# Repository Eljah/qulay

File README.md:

# Qulay / Кулай

**QL-01.R1 + C1 — открытый инженерный прототип контактного профилометра доступной среды.** Тележка с 31 независимым роликом измеряет переход «дорога — бордюрный съезд — тротуар». Результат — исходные отсчёты, геометрия, пропуски и воспроизводимый отчёт, а не неподтверждённое заключение о приёмке.

Рабочая ветка: `feature/qulay-prototype-20261002`. Исходная история сохранена; `main` не заменяется. **Это ещё не производственный комплект всей тележки и не метрологически утверждённый прибор.**

## Актуальное соединение рычага с валом: C1

Предупреждение в документах R1 о неразработанном соединении рычага с валом относится к исторической конструкции. Теперь для этого узла разработан **C1: цельный фланцевый вал, два установочных штифта Ø3 и два прижимных винта M3**. Передача момента не опирается на трение стянутых торцов. Детали, посадки, сборка и критерии стендового контроля описаны в отдельном комплекте; физические испытания ещё не выполнены.

**[PDF C1: пояснение и размерные чертежи](mechanical/coupling_c1/generated/Qulay_C1_Lever_Shaft_Coupling.pdf)** · **[Весь комплект STEP/DXF и отчётов](mechanical/coupling_c1/generated)** · **[Описание конструкции и изготовления](mechanical/coupling_c1/README.md)** · **[Область изменения C1](docs/REVISION_C1.md)**

В каталоге C1 находятся обычные файлы, а не архив вместо проекта: отдельные STEP деталей и соединения, три STEP-сборки тележки с установленным C1, DXF рычага и карты отверстий фланца, PDF, BOM, расчёт, проверка пересечений и контрольные суммы. Старые модели R1 сохранены для сравнения; они не заменяют сборки с C1.

## Что открывать

| Часть | Содержимое |
|---|---|
| [C1: соединение рычага с валом](mechanical/coupling_c1) | Цельный фланцевый вал, штифты и винты; исходники, детали, посадки и порядок сборки |
| [C1: готовые файлы](mechanical/coupling_c1/generated) | PDF с тремя листами A3, STEP деталей и трёх положений тележки, DXF, BOM и проверки |
| [Руководство по механике и монтажу R1](docs/manual) | Историческая базовая инструкция; для соединения рычаг–вал применять дополнение C1 |
| [Один ролик, tilt и AS5048A](docs/channel) | Принцип измерения, магнит, SPI и преобразование угла; статус соединения уточнён ссылкой на C1 |
| [CAD ревизии R1](mechanical/generated-r1) | Три исторические STEP-сборки, реальные CAD-виды и разрез, DXF кронштейна, реестры, отчёты пересечений |
| [PDF узла и сборок R1](mechanical/generated-r1/QL01-R1-review.pdf) | Крупные изображения исходной ревизии; соединение рычаг–вал заменено в C1 |
| [Первоначальный комплект](mechanical/generated) | Исходные модели, альбом A3, DXF рычага и реестры; не удалены |
| [Плата датчика](electronics/generated/encoder) | KiCad-проект, схема PDF, PCB/SVG, Gerber/Excellon прототипа, ERC/DRC и netlist |
| [Плата сбора с Pico](electronics/generated/carrier) | KiCad-проект R1 для подключения четырёх цепочек датчиков, ADXL355-модуля, одометра и USB |
| [Прошивка](firmware) | RP2040/Pico SDK, сборка UF2/ELF в Actions; C, не Java |
| [Java/Maven](software) | core, сервер Spring Boot, desktop Swing, агент SBC и геометрический симулятор |
| [Подтверждение тестов R1](generated/verification/summary.json) | 52 модульных теста и 12 end-to-end проверок на момент R1; commit и run ID внутри отчёта |
| [Изменения и ограничения R1](docs/REVISION_R1.md) | История исправлений и исходные ограничения; дополнение по соединению — C1 |

Редактируемый CAD-источник C1: [mechanical/coupling_c1/build.py](mechanical/coupling_c1/build.py), использующий [mechanical/revision_b.py](mechanical/revision_b.py) и исходный [build.py](mechanical/build.py). Это CadQuery/OpenCascade + STEP, не вымышленный проект, якобы сохранённый из SolidWorks.

## Архитектура базового программно-измерительного контура R1

```mermaid
flowchart LR
  Rollers[31 ролик + AS5048A] -->|SPI: 8+8+8+7| Pico[Pico / RP2040 · C]
  Tilt[ADXL355-модуль] -->|SPI| Pico
  Odo[Одометр 3.3 V] --> Pico
  Pico -->|USB CDC + CRC32| SBC[Linux SBC · Java 21]
  SBC -->|Wi-Fi / HTTPS| Server[Spring Boot · планы и обследования]
  SBC -->|JSON + SHA-256 + сырой журнал| USB[Съёмный накопитель]
  USB --> Desktop[Swing · просмотр и загрузка]
  Desktop -->|HTTPS| Server
  Server -->|План обследования| Desktop
  Desktop -->|План + SHA-256| USB
```

Основной компьютер — Raspberry Pi/совместимый Linux SBC; измерительный опрос вынесен в Pico. Специальное мобильное приложение не требуется: телефон может предоставлять Wi-Fi-точку доступа. Полностью автономный мобильный интернет предполагает отдельный USB LTE-модем и настройку Linux; собственная ВЧ-плата и проверенный LTE-комплект в R1 не заявлены. Выпуск C1 изменяет механическое соединение, а не этот контур связи.

## Что измеряется

X — направление прохода, Y — положение канала поперёк тележки, Z — высота. Угол рычага — исходное измерение, **не ось Y и не готовый уклон поверхности**. При пересчёте изменяются и X, и Z точки контакта; наклоны рамы также учитываются.

`CROSSING`: движение поперёк бордюра. Для достоверного продольного профиля нужна независимая высотная база. `ALONG_CURB`: часть роликов на дороге, часть на тротуаре; анализируется разность площадок и смещение контактов по X. `FREE_ROLL` не становится строгим продольным нивелированием только благодаря IMU.

Габариты проекта: 31 канал × шаг 25 мм; 750 мм между крайними осями; наружная ширина по осям крепежа 870 мм; рычаг 240 мм; ролики с короной R20, ширина 12 мм. Это принятые проектные значения, не универсальные нормативы размеров инвалидного кресла.

Одного прохода шириной 750 мм недостаточно для доказательства доступности всей ширины съезда. Вертикальная грань, потеря контакта и ненаблюдаемая область сохраняются как отдельные состояния, а не превращаются сглаживанием в удобный пандус.

## Сборка и запуск

Нужны **JDK 21 и Maven**. Старые JDK 12/17 не соответствуют текущей сборке.

```bash
git clone --branch feature/qulay-prototype-20261002 https://github.com/Eljah/qulay.git
cd qulay
mvn -B verify
java -jar software/simulator/target/simulator-0.1.0.jar generated/demo
java -jar software/desktop/target/desktop-0.1.0.jar
```

В desktop откройте JSON из `generated/demo/surveys` рядом с его `.sha256`. Есть матрица всех 31 каналов, выбор продольного профиля, отдельный просмотр сырых углов, выгрузка CSV, загрузка на сервер и запись плана на флешку. Серые ячейки — недостоверные/пропущенные точки. Данные симулятора явно отмечены как синтетические.

Сервер Linux/macOS:

```bash
export QULAY_TOKEN="$(openssl rand -hex 32)"
java -jar software/server/target/server-0.1.0.jar
```

Windows PowerShell:

```powershell
$env:QULAY_TOKEN = [guid]::NewGuid().ToString('N') + [guid]::NewGuid().ToString('N')
java -jar software/server/target/server-0.1.0.jar
```

Веб-интерфейс: `http://127.0.0.1:8080/`. Введите свой токен. Для удалённого доступа нужен HTTPS reverse proxy и отдельная настройка безопасности. У сервера нет универсального встроенного пароля; по умолчанию он слушает только loopback. Перед публичным развёртыванием требуется проверка актуальности зависимостей и эксплуатационный аудит.

Загрузка накопленных проходов:

```bash
java -jar software/agent/target/agent-0.1.0.jar sync generated/demo/surveys http://127.0.0.1:8080
```

Команда использует `QULAY_TOKEN` из окружения. Повторная отправка тех же байтов идемпотентна. Другие данные с тем же UUID отвергаются.

## Захват с реальной платы

Сначала получите план из сервера через desktop или `agent pull-plan`. Для захвата нужен `plan.json` с парным `.sha256`, а также индивидуальная калибровка 31 канала, не синтетический шаблон.

```bash
java -jar software/agent/target/agent-0.1.0.jar capture /dev/ttyACM0 calibration.json plan.json 1000 /media/usb/QULAY/surveys 10 0
```

Последние параметры: тайм-аут полного кадра в секундах и индекс объекта плана с нуля. Незавершённый проход остаётся `.wire.partial`; законченный получает JSON/SHA-256 и сырой журнал. Устройства в Q1 ещё не имеют подтверждённого контроля контакта: CONTACT_UNKNOWN сохраняется и блокирует положительное заключение.

## Проверки, которые действительно выполняются

**Программа:** модульные тесты геометрии, CRC, обработки данных, тайм-аутов и неполных проходов. E2E поднимает реальный JVM-сервер, проверяет авторизацию, хеши, повторы, конфликт UUID, планы, синхронизацию и сохранность после перезапуска. Скриншоты — пиксели настоящего окна Swing в Xvfb с синтетическим входом.

**Электроника:** реально запущены трассировщик и KiCad. Проверяются ERC, DRC, отсутствие неразведённых соединений и соответствие каждого подключённого вывода исходной таблице, схеме и PCB. [Отчёт R1](electronics/generated/verification-summary.json). Это не аналоговая симуляция и не испытание собранной платы.

**Механика R1:** три соседних канала в трёх статических положениях проверяются на пересечения твёрдых тел. [Отчёт R1](mechanical/generated-r1/collision-checks.json) и [проблемы исходной сборки](mechanical/generated-r1/original-interference.json). Это не FEA и не проверка всех зазоров тележки во всём диапазоне движения.

**Соединение C1:** сохранены [проверка твёрдых тел и 19 угловых положений](mechanical/coupling_c1/generated/verification.json) и [расчёт с консервативным нагружением одного штифта](mechanical/coupling_c1/generated/calculations.json). Отчёты относятся к указанному узлу и сохранённым соседям R1. Статический расчёт и CAD-проверка не подтверждают ресурс и фактический люфт изготовленного экземпляра.

Бинарные JAR/UF2/ELF и полные журналы доступны в [GitHub Actions](https://github.com/Eljah/qulay/actions). Артефакты Actions имеют срок хранения; CAD, схемы, отчёты и исходники сохранены также обычными файлами Git. Скрипт публикации не делает force-push и отказывается публиковать устаревшую сборку при изменении её входных файлов.

## До полевой приёмки

Соединение рычага с валом конструктивно определено выпуском C1; остаются изготовление согласованной пары и физический контроль. Не закрыты физические испытания трёхканального узла, осевая фиксация всего вала в корпусе, окончательное крепление магнита, реальные пружины/замки/уплотнения и прочий крепёж, контроль контакта, калибровка магнитных датчиков, проверка высотной базы под нагрузкой и методика оценки неопределённости. Профиль `DEMO-ONLY-01` — демонстрационный, не набор подтверждённых нормативных пределов. `acceptanceEligible` остаётся false.

[Концепция](docs/CONCEPT.md) · [Метрология](docs/METROLOGY.md) · [Подробности R1](docs/REVISION_R1.md) · [Соединение C1](docs/REVISION_C1.md) · [Прошивка и распиновка](firmware/README.md)

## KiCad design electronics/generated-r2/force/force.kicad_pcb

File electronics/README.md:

# Электронная сборка QL-01

## Архитектура

Raspberry Pi 4 / Linux SBC выполняет Java-агент, хранение, связь и работу с флеш-памятью. Pico RP2040 подключён к нему по USB CDC и опрашивает измерительные датчики. Специальное мобильное приложение не требуется: телефон может предоставить Wi-Fi hotspot; опционально используется готовый сертифицированный USB LTE-модем. Разработка собственного GSM-тракта не входит в QL-01.

Редактируемые проекты KiCad создаются `build_checked.py`: плата углового датчика `encoder` 18×24 мм, плата сопряжения Pico `carrier` 80×100 мм. Схемы и платы создаются из одной таблицы выводов, поэтому в `connections.csv` есть явная проверяемая карта каждого контакта. `harness.csv` задаёт все 31 канала, цепочки 8+8+8+7. Изображение платы без электрических сетей не выдаётся за разработанную схему.

## Основные узлы и количества

| Узел | Количество | Примечание |
|---|---:|---|
| Raspberry Pi 4 / Linux SBC | 1 | Java 21, USB, Wi-Fi; отдельное питание |
| Raspberry Pi Pico RP2040 | 1 | Нативный USB; две SPI-шины |
| AS5048A, TSSOP14 | 31 | По одному на каждый шарнир |
| encoder PCB | 31 | AS5048A, 100 нФ, 10 мкФ, разъём |
| carrier PCB | 1 | Разъёмы Pico, датчиков, питания, одометра |
| Диаметрально намагниченный магнит | 31 | Геометрия и материал согласуются по испытанию |
| ADXL355, модуль с доступным SPI 3.3 В | 1 | Жгут согласно нашей распиновке; не обещается прямое совпадение с любым модулем |
| Квадратурный энкодер 3.3 В | 1 | Реальное колесо и масштаб калибруются; 12/24 В входы не поддержаны |
| Внешний стабилизатор датчиков 3.3 В | 1 | Ток не менее 1 А как проектный запас, с ограничением тока |
| Питание SBC 5 В | 1 | Проектный бюджет до 4 А с запасом и отдельной проверкой пиков USB |
| Готовая батарея с BMS/защитой | 1 | Не проект самостоятельной сборки литиевых ячеек |

31 AS5048A при типовом потреблении порядка 15 мА требуют около 465 мА, без запаса. Не подключать их все к 3V3 Pico. Carrier принимает отдельные 3.3 В через PTC; номинал PTC и температурное снижение допустимого тока должны быть проверены. Pico питается от USB, общая земля соединена. Отключённое питание датчиков при активных SPI-линиях может вызывать паразитное питание через входы: порядок включения, буфер/изоляция и защита линий подлежат проверке перед полевым прибором.

Оценочный рабочий бюджет всей электроники 12–20 Вт, не измеренный. Для батареи 60 Вт·ч и суммарного использования 80% это примерно 2.4–4 часа; холод и LTE могут ухудшить результат. Номинал батареи выбирается после замера фактического потребления и пиков.

## Монтаж и первичное включение

Сначала USB-Pico без датчиков: загрузить UF2, проверить CDC и период строк. Затем один AS5048A от ограниченного источника 3.3 В; проверить распиновку, паритет, OCF и диагностику магнита при полном диапазоне поворота. Затем три соседних канала и влияние магнитов. Только после этого — все цепочки и нагрузочное питание. Физическое движение одного рычага должно менять именно его индекс в журнале, иначе порядок SPI-цепочки не подтверждён.

AS5048A SPI mode 1, ADXL355 SPI mode 0: они намеренно на разных контроллерах. Жгуты сигнала и земли прокладывать совместно, питание вести с достаточным сечением; окончательные длины, фронты, резисторы согласования, ESD и EMC подтверждаются на приборе. Наружный USB и разъёмы должны иметь механическую разгрузку и защиту от воды. Защита IP в QL-01 не заявляется.

## Что проверяет автоматическая сборка

KiCad 9, проверка сериализованных координат каждой площадки, экспорт DSN, реальная трассировка Freerouting, обратный импорт SES, DRC, ERC, экспорт схем в PDF и платы в SVG. Все сообщения сохраняются; они не скрываются исключениями. Наличие файлов Gerber, если они экспортированы, не является разрешением на производство: `manufacturing_release=false` остаётся до независимой проверки питания, контактов, схемы, EMC и магнитной калибровки.

Скрипт `build.py` — генератор логической модели; запускать именно `build_checked.py`, который нормализует координаты площадок через API KiCad 9 и повторно читает сохранённую плату. Это исправляет выявленную несовместимость KiCad 7. Системный Python должен содержать pcbnew. Пересборка: `python3 electronics/build_checked.py`, трассировка DSN в SES, `python3 electronics/verify.py`.

## Нереализованные аппаратные функции

Нет валидированного датчика контакта/усилия каждого ролика. Нет интерфейса внешнего геодезического Z, температурной компенсации, защищённого полевого питания и сертифицированного корпуса. Q1 сохраняет реальные углы/ускорение/пробег, но не имеет права утверждать, что все ролики касались покрытия. Эти ограничения отражены в данных, а не спрятаны в документации.

Первичные источники: [AS5048A](https://www.infineon.com/assets/row/public/documents/24/49/infineon-as5048a-as5048b-datasheet-en.pdf), [ADXL355](https://www.analog.com/media/en/technical-documentation/data-sheets/adxl354_adxl355.pdf), [Pico SDK](https://www.raspberrypi.com/documentation/pico-sdk/hardware.html), [KiCad Ubuntu](https://www.kicad.org/download/details/ubuntu/). Отчёты в `generated/` относятся к точной сохранённой ревизии плат.

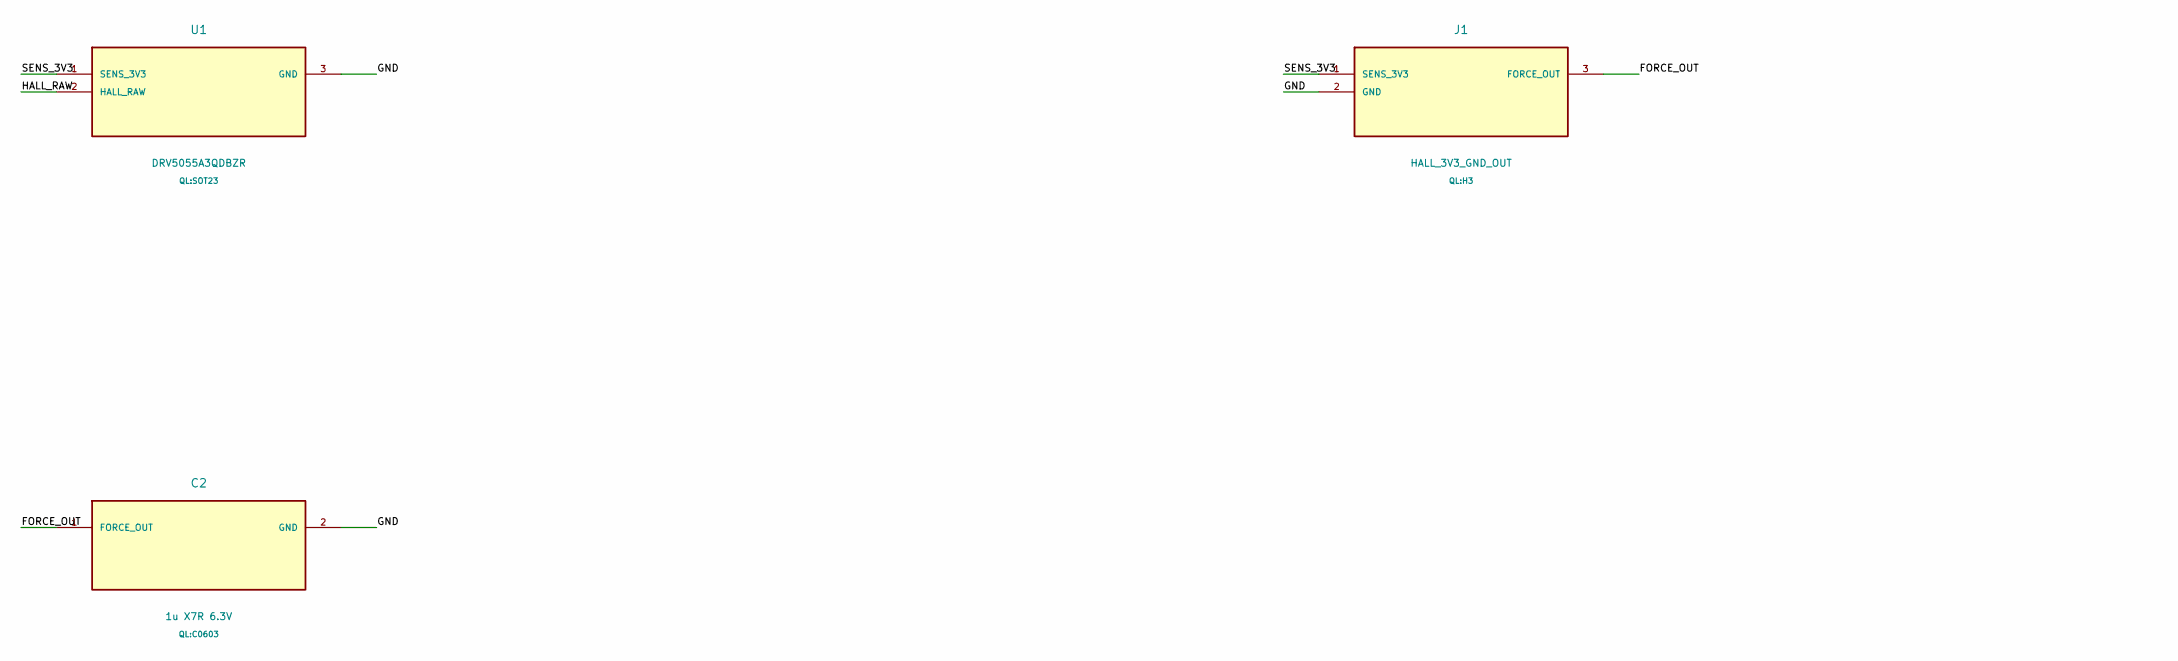
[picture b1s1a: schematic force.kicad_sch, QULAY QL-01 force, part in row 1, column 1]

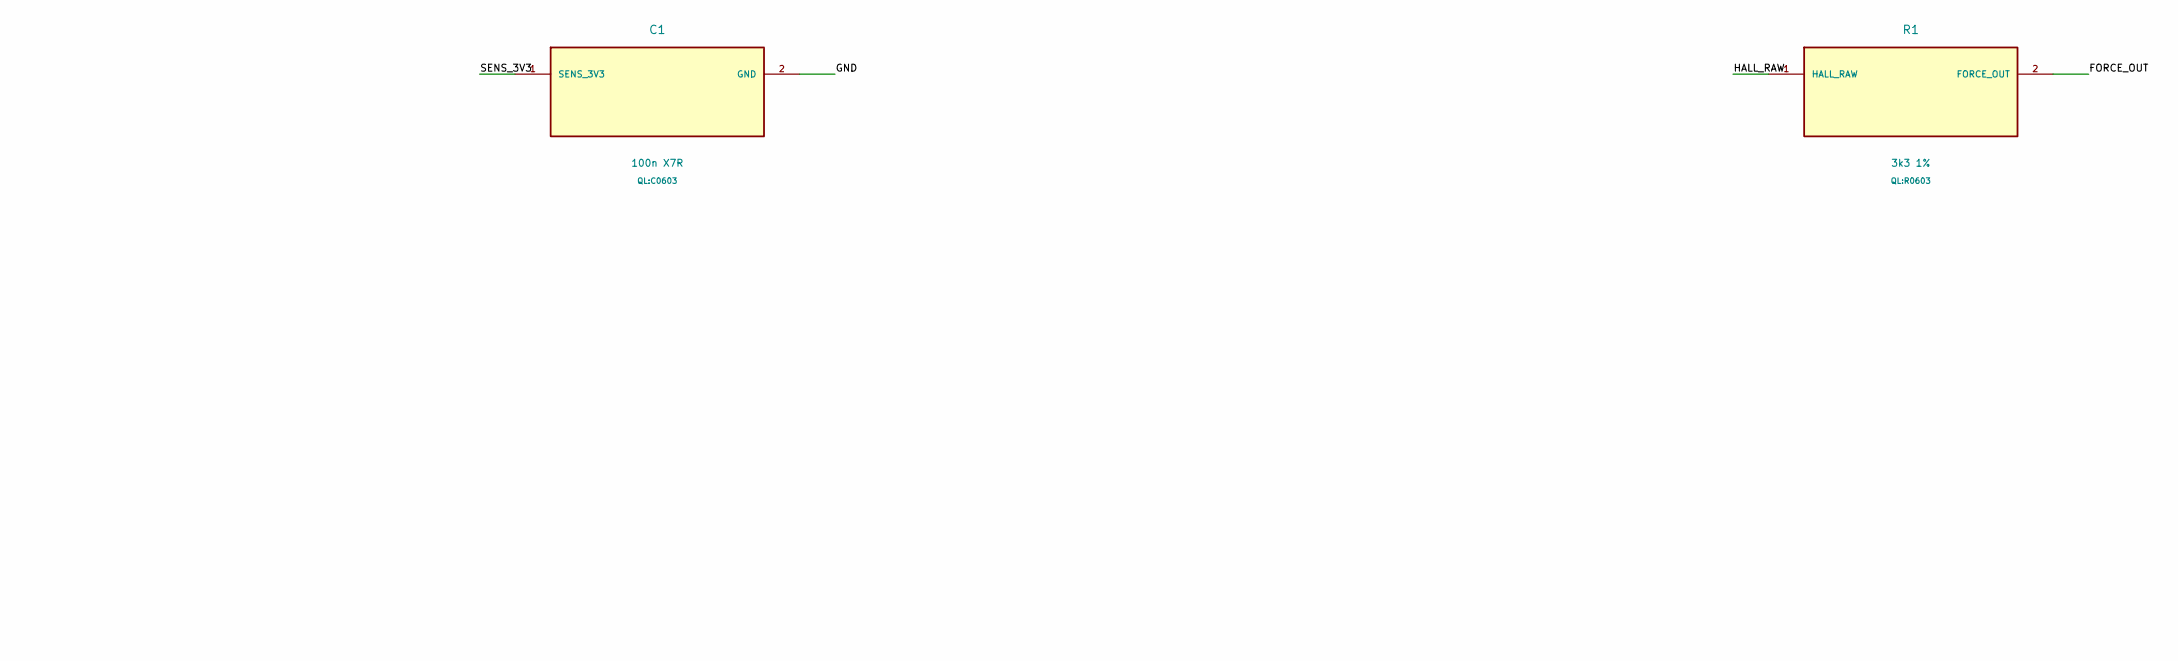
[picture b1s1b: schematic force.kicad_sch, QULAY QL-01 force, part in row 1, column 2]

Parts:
C1: 100n X7R; C0603
C2: 1u X7R 6.3V; C0603
J1: HALL_3V3_GND_OUT; H3
R1: 3k3 1%; R0603
U1: DRV5055A3QDBZR; SOT23

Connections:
FORCE_OUT: C2.1 (FORCE_OUT), J1.3 (FORCE_OUT), R1.2 (FORCE_OUT)
GND: C1.2 (GND), C2.2 (GND), J1.2 (GND), U1.3 (GND)
HALL_RAW: R1.1 (HALL_RAW), U1.2 (HALL_RAW)
SENS_3V3: C1.1 (SENS_3V3), J1.1 (SENS_3V3), U1.1 (SENS_3V3)

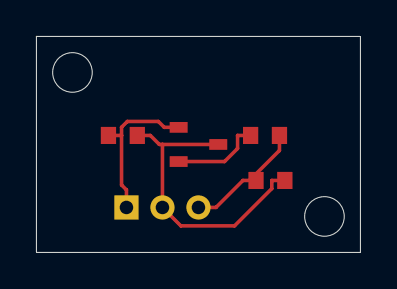
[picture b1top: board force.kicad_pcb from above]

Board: 2 copper layers, 18.0 x 12.0 mm, 7 parts (0 on the bottom side), 4 nets.

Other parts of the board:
MH1, MH2: MountingHole_2.2mm

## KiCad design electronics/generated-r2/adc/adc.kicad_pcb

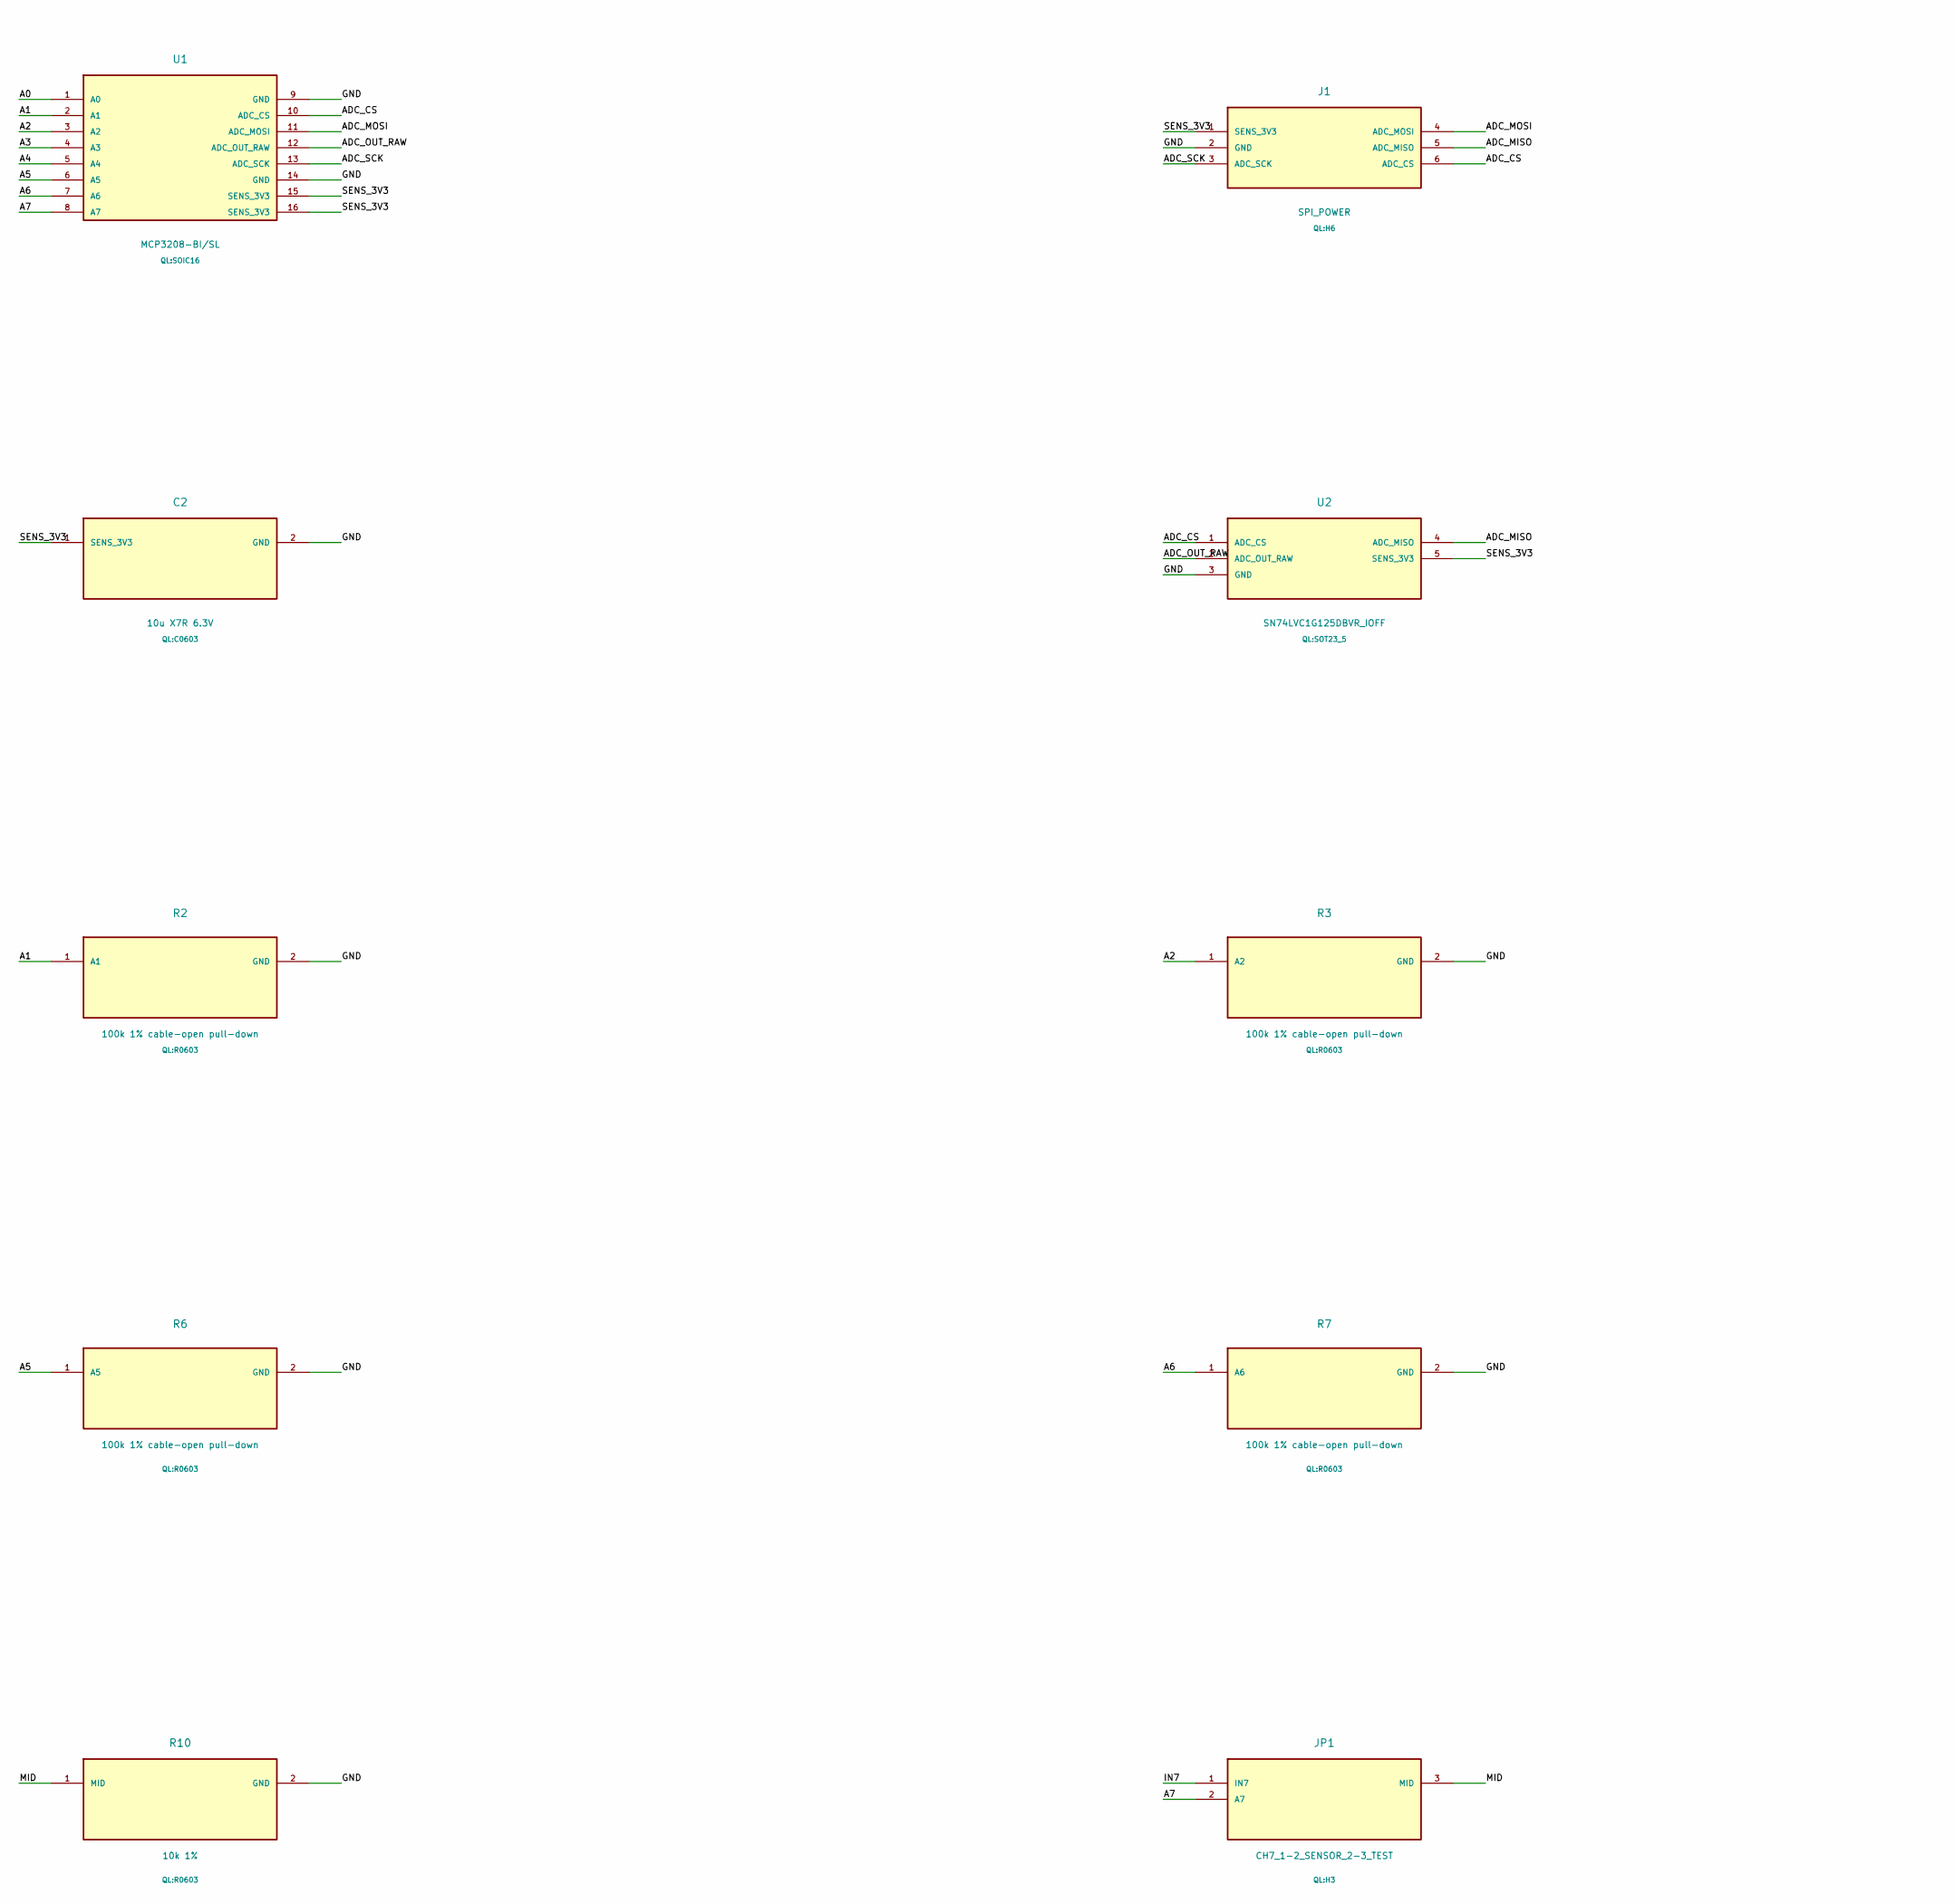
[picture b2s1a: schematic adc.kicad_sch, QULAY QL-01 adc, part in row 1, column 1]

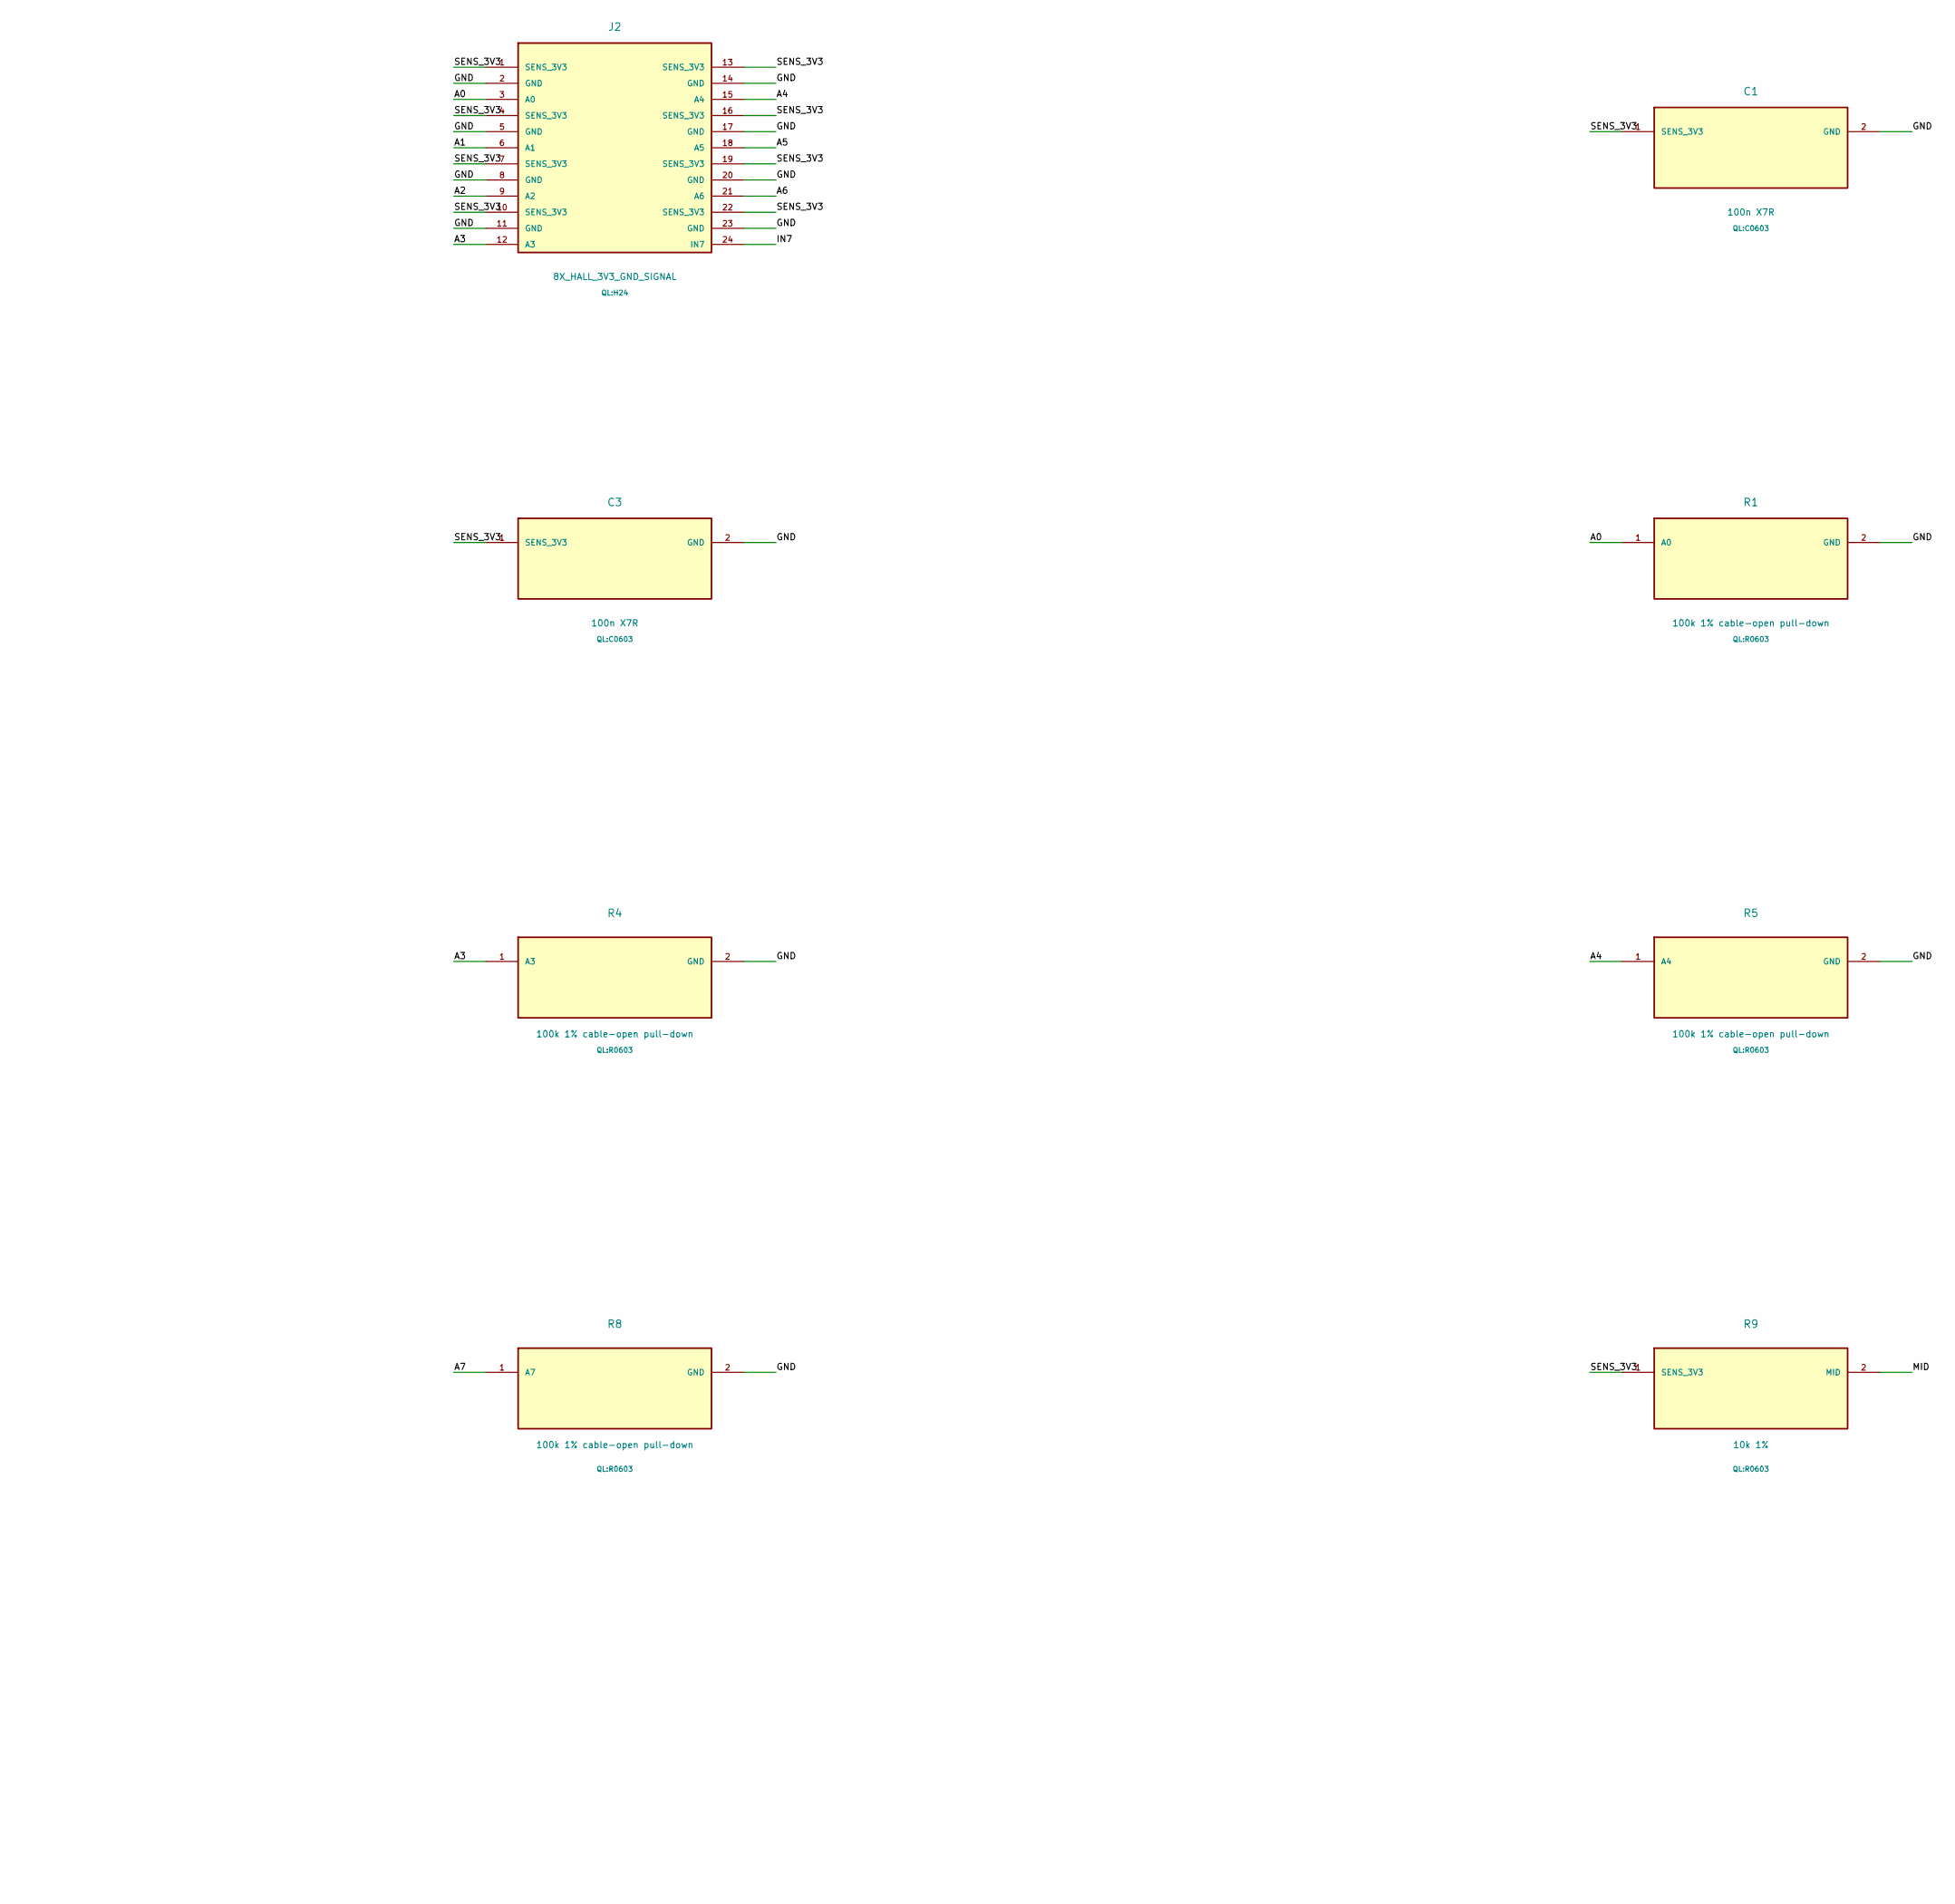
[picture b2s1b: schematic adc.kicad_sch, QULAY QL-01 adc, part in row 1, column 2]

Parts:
C1, C3: 100n X7R; C0603
C2: 10u X7R 6.3V; C0603
J1: SPI_POWER; H6
J2: 8X_HALL_3V3_GND_SIGNAL; H24
JP1: CH7_1-2_SENSOR_2-3_TEST; H3
R1, R2, R3, R4, R5, R6, R7, R8: 100k 1% cable-open pull-down; R0603
R9, R10: 10k 1%; R0603
U1: MCP3208-BI/SL; SOIC16
U2: SN74LVC1G125DBVR_IOFF; SOT23_5

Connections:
A0: J2.3 (A0), R1.1 (A0), U1.1 (A0)
A1: J2.6 (A1), R2.1 (A1), U1.2 (A1)
A2: J2.9 (A2), R3.1 (A2), U1.3 (A2)
A3: J2.12 (A3), R4.1 (A3), U1.4 (A3)
A4: J2.15 (A4), R5.1 (A4), U1.5 (A4)
A5: J2.18 (A5), R6.1 (A5), U1.6 (A5)
A6: J2.21 (A6), R7.1 (A6), U1.7 (A6)
A7: JP1.2 (A7), R8.1 (A7), U1.8 (A7)
ADC_CS: J1.6 (ADC_CS), U1.10 (ADC_CS), U2.1 (ADC_CS)
ADC_MISO: J1.5 (ADC_MISO), U2.4 (ADC_MISO)
ADC_MOSI: J1.4 (ADC_MOSI), U1.11 (ADC_MOSI)
ADC_OUT_RAW: U1.12 (ADC_OUT_RAW), U2.2 (ADC_OUT_RAW)
ADC_SCK: J1.3 (ADC_SCK), U1.13 (ADC_SCK)
GND: C1.2 (GND), C2.2 (GND), C3.2 (GND), J1.2 (GND), J2.2 (GND), J2.5 (GND), J2.8 (GND), J2.11 (GND), J2.14 (GND), J2.17 (GND), J2.20 (GND), J2.23 (GND), R1.2 (GND), R2.2 (GND), R3.2 (GND), R4.2 (GND), R5.2 (GND), R6.2 (GND), R7.2 (GND), R8.2 (GND), R10.2 (GND), U1.9 (GND), U1.14 (GND), U2.3 (GND)
IN7: J2.24 (IN7), JP1.1 (IN7)
MID: JP1.3 (MID), R9.2 (MID), R10.1 (MID)
SENS_3V3: C1.1 (SENS_3V3), C2.1 (SENS_3V3), C3.1 (SENS_3V3), J1.1 (SENS_3V3), J2.1 (SENS_3V3), J2.4 (SENS_3V3), J2.7 (SENS_3V3), J2.10 (SENS_3V3), J2.13 (SENS_3V3), J2.16 (SENS_3V3), J2.19 (SENS_3V3), J2.22 (SENS_3V3), R9.1 (SENS_3V3), U1.15 (SENS_3V3), U1.16 (SENS_3V3), U2.5 (SENS_3V3)

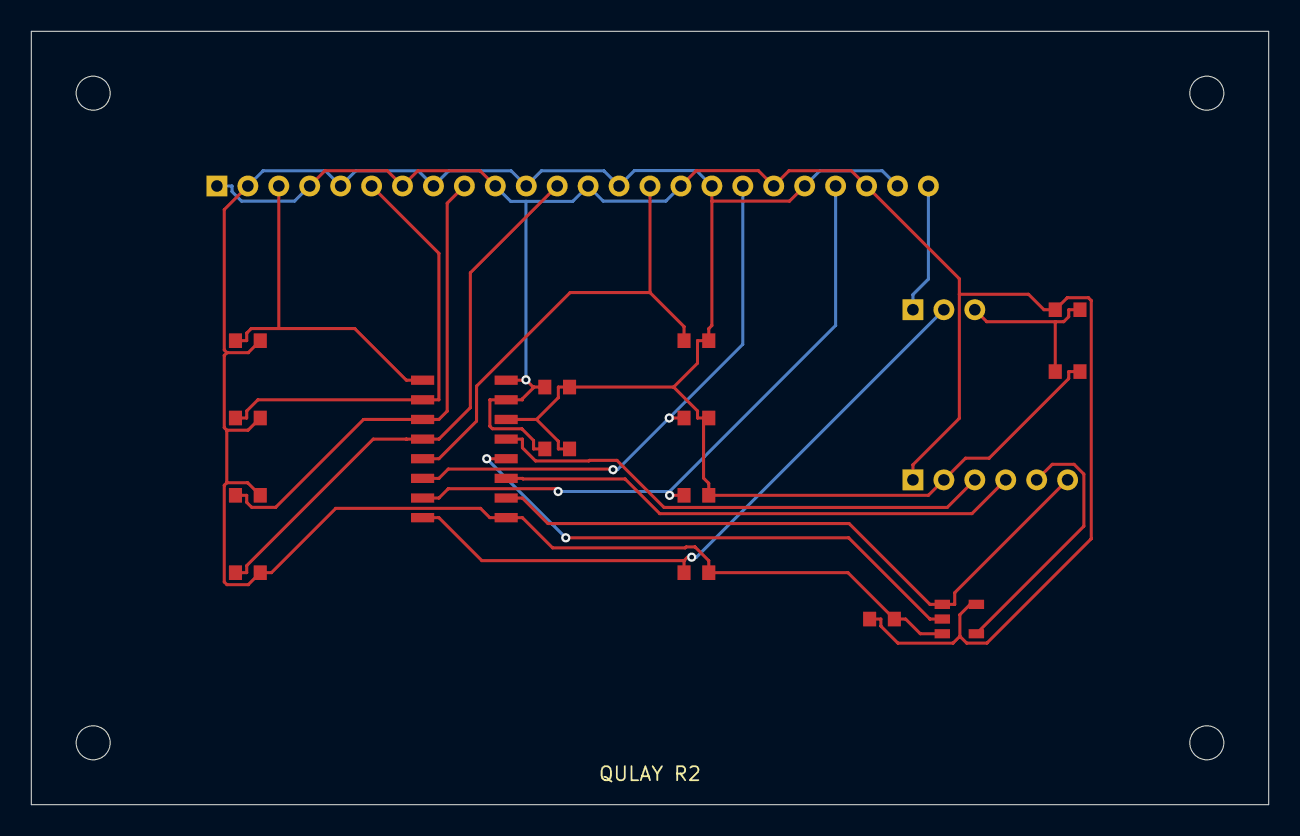
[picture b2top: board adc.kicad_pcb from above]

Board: 2 copper layers, 80.0 x 50.0 mm, 22 parts (0 on the bottom side), 17 nets.

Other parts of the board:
MH1, MH2, MH3, MH4: MountingHole_2.2mm

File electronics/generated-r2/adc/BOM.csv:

reference,value,footprint,quantity_per_board
U1,MCP3208-BI/SL,SOIC16,1
J1,SPI_POWER,H6,1
J2,8X_HALL_3V3_GND_SIGNAL,H24,1
C1,100n X7R,C0603,1
C2,10u X7R 6.3V,C0603,1
U2,SN74LVC1G125DBVR_IOFF,SOT23_5,1
C3,100n X7R,C0603,1
R1,100k 1% cable-open pull-down,R0603,1
R2,100k 1% cable-open pull-down,R0603,1
R3,100k 1% cable-open pull-down,R0603,1
R4,100k 1% cable-open pull-down,R0603,1
R5,100k 1% cable-open pull-down,R0603,1
R6,100k 1% cable-open pull-down,R0603,1
R7,100k 1% cable-open pull-down,R0603,1
R8,100k 1% cable-open pull-down,R0603,1
R9,10k 1%,R0603,1
R10,10k 1%,R0603,1
JP1,CH7_1-2_SENSOR_2-3_TEST,H3,1

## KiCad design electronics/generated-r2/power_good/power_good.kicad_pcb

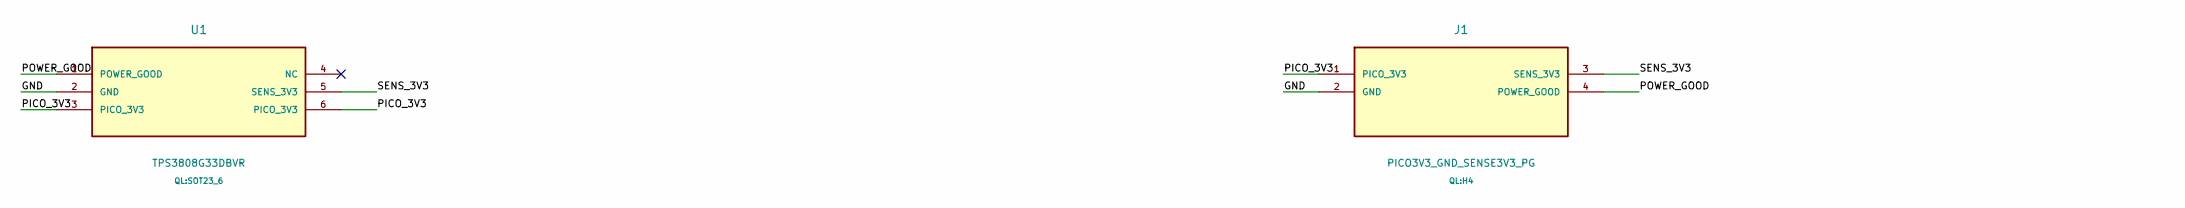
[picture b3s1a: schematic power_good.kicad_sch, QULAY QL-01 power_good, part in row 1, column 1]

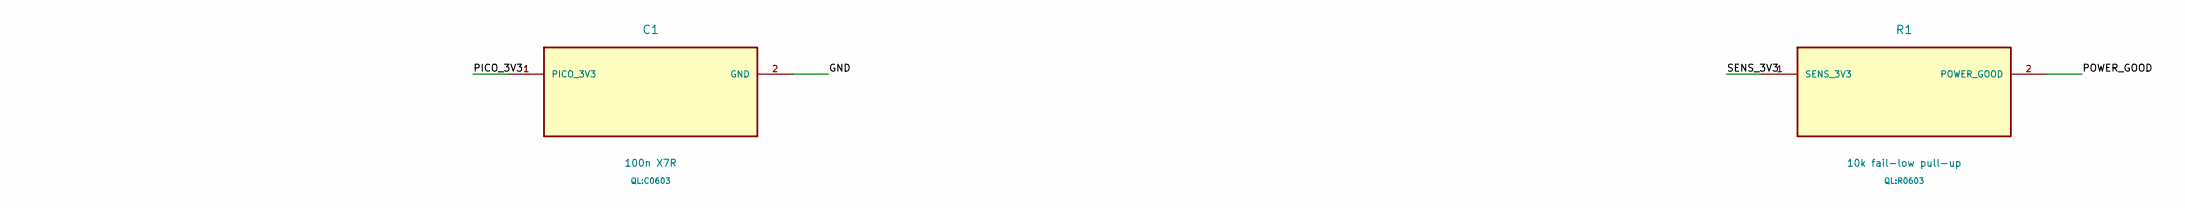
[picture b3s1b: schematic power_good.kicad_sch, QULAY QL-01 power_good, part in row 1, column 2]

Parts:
C1: 100n X7R; C0603
J1: PICO3V3_GND_SENSE3V3_PG; H4
R1: 10k fail-low pull-up; R0603
U1: TPS3808G33DBVR; SOT23_6

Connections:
GND: C1.2 (GND), J1.2 (GND), U1.2 (GND)
PICO_3V3: C1.1 (PICO_3V3), J1.1 (PICO_3V3), U1.3 (PICO_3V3), U1.6 (PICO_3V3)
POWER_GOOD: J1.4 (POWER_GOOD), R1.2 (POWER_GOOD), U1.1 (POWER_GOOD)
SENS_3V3: J1.3 (SENS_3V3), R1.1 (SENS_3V3), U1.5 (SENS_3V3)

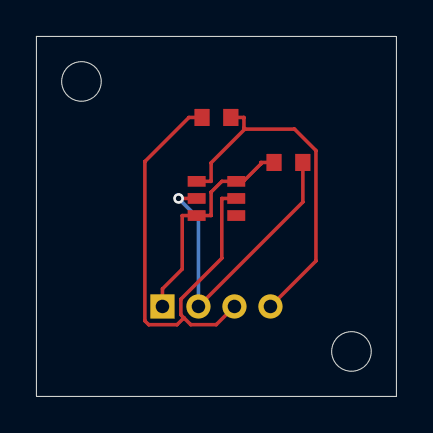
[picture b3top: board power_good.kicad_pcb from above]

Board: 2 copper layers, 20.0 x 20.0 mm, 6 parts (0 on the bottom side), 4 nets.

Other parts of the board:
MH1, MH2: MountingHole_2.2mm
